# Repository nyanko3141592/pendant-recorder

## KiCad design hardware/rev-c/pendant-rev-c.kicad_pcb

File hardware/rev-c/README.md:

# Rev C0 — 小ささ優先 / USB / 16時間録音を目指す回路

**設計検討版、発注不可。** [V1の範囲](../../docs/v1-scope.md)を優先する。Rev A/Bを上書きしない。回路図、接続表、実フットプリント配置、配線試行、収納モデルを追加した。寸法と電池持ちの成立を保証するものではない。

## 原本

- [回路図PDF](pendant-rev-c.pdf) / [KiCad回路図](pendant-rev-c.kicad_sch) / [SVG](pendant-rev-c.svg)
- [design.json](design.json) / [全端子接続表](connections.csv) / [BOM](bom.csv)
- [KiCad PCB](pendant-rev-c.kicad_pcb) / [部品配置](placement-report.json)
- [検証・発注条件](order-status.json) / [DRC](drc.json) / [ERC](erc.json)
- [ケース構造](../../mechanical/structure-c0/README.md) / [同縮尺比較](../../mechanical/size-comparison-c0/README.md)

## 現時点の検査

ERC 0、回路図とPCBの等価性差分0、260物理パッドのネット所属一致。DRC 5（USB穴クリアランス4、行き止まり配線1）、未接続67。配線は未完了で発注不可。チェックの成功は電気動作・16h動作の検証ではない。

## 回路の変更

76参照（実装部品69点＋基板接点7点）。無線モジュールをSTM32U535CEU6（UFQFPN48、7×7mm、512KB Flash/274KB SRAM、内部LDO版）へ変更。無線回路・アンテナ・RF空間はない。SDはSPIを維持し、48ピン品にSDMMCがない問題を回避する。これはMCU候補を使った回路設計で、量産採用・調達承認ではない。

- USB: PA11/PA12、SWD: PA13/PA14。
- マイク: PB3/PB4をADF1 CCK0/SDI0（AF3）へ。SPIと重複させない。
- SD: PA5/PA6/PA7をSPI1（AF5）、PA4をGPIO CS。
- 48ピンMCUには独立VDDUSB端子がないため、電源を**3.3V**へ変更。3.0V LDOの下限公差をUSB仕様へ当てない。電池終止・LDOドロップアウトによる使用容量減少は実測が必要。
- MAX17048とI2C周辺を外し、1MΩ＋1MΩ分圧と10nFでPA1へ電池電圧を入力。最大4.2Vから2.1V、定常分圧負荷2.1µA。概算残量のみ。VREFINT校正・ADC取得時間・入力漏れとRC整定を検証する。
- USB保護を同シリーズのUSBLC6-2P6/SOT-666へ小型化。ST機能端子表を参照。実装向き・ランド・受理は最終監査待ち。
- T5838＋1.8V LDO＋TXS0104EPWR、4GB SPI SD NAND、BQ25101約21.8mA、NTC＋充電停止、USB負荷分離、保護付き110mAh電池を維持。
- 録音LED＋状態LED、1ボタン。画面・キャラ・無線は追加しない。
- LSE＋内部クロック/USB CRSで動作を検討。水晶・負荷容量・USBクロック精度は未検証。

## サイズ・電力

21×31×0.8mmの4層両面基板へ実フットプリントを配置。上面にUSBとPH端子、裏面に低背部品を置く。電池は基板下へ重ねる。ケース案23.8×34×14mmで、Rev B比で長さ12.5mm減、幅1mm減、厚さ1.2mm増、直方体包絡体積約23%減。22×34×12mmの目標は達成していない。部品が置けたことと配線・組立可能性は別。

110mAh×仮使用率70%=77mAh。16hは電池端平均4.8125mA以下、20hは3.85mA以下という計算条件。3.3V化後の使用率70%は未検証で、実測時間の見積もりとして断定しない。平均2mA/3mA等を実測値として扱わない。

## 発注前の主要残件

- 全結線/DRC、USB差動配線、GND帰路、電源幅、ピン直近デカップリング。自動配置・配線の結果を電気的完成扱いにしない。
- 全ピンと代替機能の独立監査。MCUピン番号はKiCad公式ライブラリから抽出、ST DS14217と最終全数照合待ち。USB共有電源・ADC・起動・低電圧復帰を実機検証。
- 全品番/公差/高さ/在庫/JLC Standard両面実装受理。TBDの水晶、LED等を確定。ソース・BOMに載せただけで購入可能としない。
- PH嵌合プラグ、100mmの未加工線、セル膨張、NTC熱接触、底面マイク音道、ふた固定、紐/クリップ、USBプラグ挿抜クリアランス。
- 16h録音・36h保存・充電中録音・暗号・電源断・3 OS同期。これらのファームは未実装。

## 出典

2026-10-24確認。
- ST: https://www.st.com/en/microcontrollers-microprocessors/stm32u535ce.html
- STM32データシート: https://www.st.com.cn/resource/en/datasheet/stm32u535cb.pdf （DS14217 Rev5、パッケージ/端子/AF表）
- ESD保護: https://www.st.com/resource/en/datasheet/usblc6-2.pdf / https://www.st.com/en/protections-and-emi-filters/usblc6-2.html
- USBLC6-2P6カタログ: https://www.lcsc.com/product-detail/C15999.html （掲載は実装受理・在庫確保ではない）
- 電池・他部品の出典はRev B、docs/battery-sourcing.mdを継承。

## 再生成

`python3 hardware/tools/create_rev_c.py` → `generate_schematic.py rev-c` → `verify_design.py <kicad-cli> rev-c`。KiCad同梱Pythonで `layout_rev_c.py` を実行すると配置から再生成し既存配線を消すため注意。`route_rev_c.py export/import` はローカルFreerouting試行用。最新版の発注可否はorder-status.jsonを読む。

最終メタデータ同期は `sync_rev_c_metadata.py`、検査と発注不可レポート更新はKiCad Pythonで `check_rev_c.py`（未達時exit 2）。

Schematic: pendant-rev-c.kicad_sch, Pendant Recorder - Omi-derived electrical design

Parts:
C1, C2, C3, C6, C9, C22, C23, C24, C26: 100n; C_0402_1005Metric
C4: 10u; C_0603_1608Metric
C5, C15: 4.7u; C_0603_1608Metric
C7, C16, C18, C19, C25: 1u; C_0402_1005Metric
C11, C12: 10p tentative; C_0402_1005Metric
C13: 2.2u 10V; C_0402_1005Metric
C14: 2.2u; C_0402_1005Metric
C27: 22u effective TBD; C_0603_1608Metric
C28: 10n; C_0402_1005Metric
D1: red LED; LED_0402_1005Metric
D2: BAT54WS (candidate; leakage/forward drop review p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; D_SOD-323
D6: amber LED 0402 TBD; LED_0402_1005Metric
J1: USB4105-GF-A (candidate); USB_C_Receptacle_GCT_USB4105-xx-A_16P_TopMnt_Horizontal
J2: S2B-PH-SM4-TB(LF)(SN) / DTP401525 110mAh; JST_PH_S2B-PH-SM4-TB_1x02-1MP_P2.00mm_Horizontal
J3: TC2030 SWD target pads; Tag-Connect_TC2030-IDC-NL_2x03_P1.27mm_Vertical
Q1: DMP2035U (candidate; power path review pending); SOT-23
Q2: 2N7002 (charge inhibit); SOT-23
Q3: 2N7002 (VBUS detect); SOT-23
R1: 0R; R_0402_1005Metric
R2: 10k; R_0402_1005Metric
R3, R4, R11, R12, R13, R15, R16, R17, R22: 100k; R_0402_1005Metric
R5: 3.3k; R_0402_1005Metric
R6, R7: 5.1k 1%; R_0402_1005Metric
R8, R9: 0R tuning; R_0402_1005Metric
R10: 6.19k 1%; R_0402_1005Metric
R14: 1M; R_0402_1005Metric
R21, R23: 22R tentative; R_0402_1005Metric
R24, R25, R28: 47k; R_0402_1005Metric
R32: 6.8k tentative; R_0402_1005Metric
R33, R34: 1M 1%; R_0402_1005Metric
SW1: B3U-1000P (candidate); SW_SPST_B3U-1000P
TH1: NCP15XH103F03RC 10k NTC; R_0402_1005Metric
TP1, TP2, TP3, TP4, TP5, TP6: TestPoint; TestPoint_Pad_D1.0mm
U1: STM32U535CEU6; QFN-48-1EP_7x7mm_P0.5mm_EP5.6x5.6mm
U2: USBLC6-2P6; SOT-666
U3: BQ25101YFPR; BQ25101_YFP6
U4: TPS7A0233PDBVR; SOT-23-5
U6: TPS7A0218PDBVR; SOT-23-5
U8: T5838; T5838_LGA7_BottomPort
U9: TXS0104EPWR; TSSOP-14_4.4x5mm_P0.65mm
U10: TPS22916CYFPR; TPS22916_YFP4
U11: CSNP32GCR01-BOW; CSNP32GCR01_LGA8
Y1: 32.768kHz CL=7pF TBD; Crystal_SMD_2012-2Pin_2.0x1.2mm

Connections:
/BAT: C14.1, J2.1 (PACK+), Q1.3 (D), R33.1, TP1.1, U3.A1 (OUT)
/BAT_ADC: C28.1, R33.2, R34.1, U1.11 (PA1)
/BAT_TS: Q2.3 (D), TH1.1, U3.B1 (TS)
/BOOT0: R3.1, U1.44 (PH3)
/BUTTON_N: R4.2, SW1.1, U1.26 (PB13)
/CC1: J1.A5 (CC1), R6.1
/CC2: J1.B5 (CC2), R7.1
/CHG_DISABLE: Q2.1 (G), R12.1, U1.20 (PB2)
/CHG_N: R11.2, U1.27 (PB14), U3.C1 (CHG)
/GND: C1.2, C2.2, C3.2, C4.2, C5.2, C6.2, C7.2, C9.2, C11.2, C12.2, C13.2, C14.2, C15.2, C16.2, C18.2, C19.2, C22.2, C23.2, C24.2, C25.2, C26.2, C27.2, C28.2, D1.1 (K), D6.1 (K), J1.A1 (GND), J1.A12 (GND), J1.B1 (GND), J1.B12 (GND), J1.SH (SHIELD), J2.2 (PACK-), J3.5 (GND), Q2.2 (S), Q3.2 (S), R3.2, R6.2, R7.2, R10.2, R12.2, R14.2, R16.2, R17.2, R22.2, R34.2, SW1.2, TH1.2, TP6.1, U1.8 (VSSA), U1.23 (VSS), U1.35 (VSS), U1.47 (VSS), U1.49 (VSS), U2.2 (GND), U3.C2 (VSS), U4.2 (GND), U6.2 (GND), U8.2 (SELECT), U8.3 (GND), U9.7 (GND), U10.B1 (GND), U11.4 (VSS)
/ISET: R10.1, U3.B2 (ISET)
/LED_A: D1.2 (A), R5.2
/LSE_IN: C11.1, U1.3 (PC14), Y1.1
/LSE_OUT: C12.1, U1.4 (PC15), Y1.2
/MIC_CLK_1V8: U8.6 (CLK), U9.5 (A4)
/MIC_DATA_1V8: U8.1 (DATA), U9.4 (A3)
/MIC_EN: R17.1, U1.19 (PB1), U6.3 (EN)
/MIC_THSEL: U1.13 (PA3), U9.12 (B2)
/MIC_THSEL_1V8: U8.5 (THSEL), U9.3 (A2)
/MIC_WAKE: U1.12 (PA2), U9.13 (B1)
/MIC_WAKE_1V8: U8.4 (WAKE), U9.2 (A1)
/NRST: C9.1, J3.3 (nRESET), R2.2, U1.7 (NRST)
/PDM_CLK: R21.2, U9.10 (B4)
/PDM_CLK_MCU: R21.1, U1.39 (PB3)
/PDM_DATA: U1.40 (PB4), U9.11 (B3)
/REC_LED: R5.1, U1.25 (PB12)
/SD_CLK: R23.2, U11.3 (CLK)
/SD_CLK_MCU: R23.1, U1.15 (PA5)
/SD_CS_N: R28.2, U1.14 (PA4), U11.2 (CS_N)
/SD_EN: R22.1, U1.18 (PB0), U10.B2 (ON)
/SD_MISO: R25.2, U1.16 (PA6), U11.6 (DO)
/SD_MOSI: R24.2, U1.17 (PA7), U11.5 (DI)
/SD_V3: C26.1, C27.1, R24.1, R25.1, R28.1, TP5.1, U10.A1 (VOUT), U11.8 (VCC)
/STATUS_LED: R32.1, U1.29 (PA8)
/STATUS_LED_A: D6.2 (A), R32.2
/SWCLK: J3.4 (SWCLK), U1.37 (PA14)
/SWDIO: J3.2 (SWDIO), U1.34 (PA13)
/SYS: C15.1, D2.1 (K), Q1.2 (S), TP2.1, U4.1 (IN), U4.3 (EN)
/USB_DM: J1.A7 (D-), J1.B7 (D-), R9.1, U2.3 (IO2), U2.4 (IO2)
/USB_DM_MCU: R9.2, U1.32 (PA11)
/USB_DP: J1.A6 (D+), J1.B6 (D+), R8.1, U2.1 (IO1), U2.6 (IO1)
/USB_DP_MCU: R8.2, U1.33 (PA12)
/V1V8: C18.1, C22.1, C23.1, TP4.1, U6.5 (OUT), U8.7 (VDD), U9.1 (VCCA), U9.8 (OE)
/V3V3: C1.1, C2.1, C3.1, C4.1, C16.1, C19.1, C24.1, C25.1, J3.1 (VTref), R1.1, R2.1, R4.1, R11.1, R15.1, TP3.1, U1.1 (VBAT), U1.24 (VDD), U1.36 (VDD), U1.48 (VDD), U4.5 (OUT), U6.1 (IN), U9.14 (VCCB), U10.A2 (VIN)
/VBUS: C13.1, D2.2 (A), J1.A4 (VBUS), J1.A9 (VBUS), J1.B4 (VBUS), J1.B9 (VBUS), Q1.1 (G), R13.1, R16.1, U2.5 (VBUS), U3.A2 (IN)
/VBUS_GATE: Q3.1 (G), R13.2, R14.1
/VBUS_N: Q3.3 (D), R15.2, U1.10 (PA0)
/VCAP: C5.1, U1.22 (VCAP)
/VDDA: C6.1, C7.1, R1.2, U1.9 (VDDA)

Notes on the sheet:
01 MCU / RTC / UI
02 USB-C / CHARGER
03 POWER / FUEL GAUGE
04 AUDIO / SD / INDICATORS
ENGINEERING DRAFT - NOT FOR FABRICATION - See hardware/rev-c/README.md

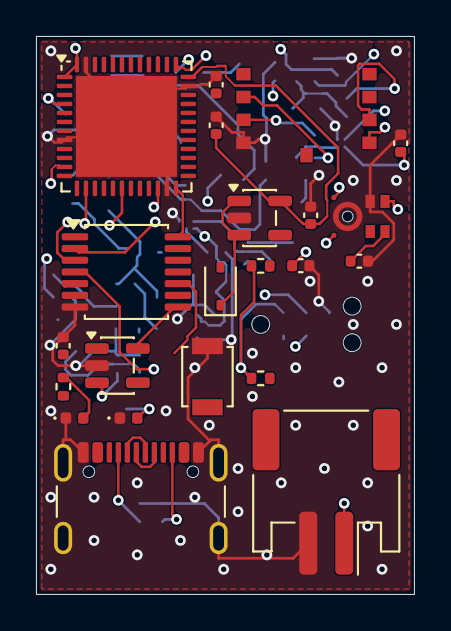
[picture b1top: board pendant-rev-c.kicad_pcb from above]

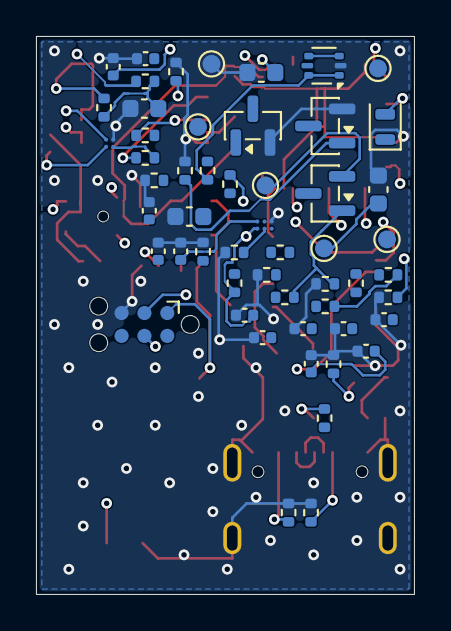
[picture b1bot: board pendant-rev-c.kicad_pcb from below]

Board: 4 copper layers, 21.0 x 31.0 mm, 76 parts (54 on the bottom side), 49 nets.

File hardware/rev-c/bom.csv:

Reference,Part/value,Footprint,Design note
U1,STM32U535CEU6,Package_DFN_QFN:QFN-48-1EP_7x7mm_P0.5mm_EP5.6x5.6mm,512KB Flash/274KB RAM; non-SMPS UFQFPN48. PB3/PB4 ADF AF3; PA5/6/7 SPI1 AF5. VDD USB shared 3.3V. JLC acceptance and pin review pending.
C1,100n,Capacitor_SMD:C_0402_1005Metric,
C4,10u,Capacitor_SMD:C_0603_1608Metric,Main bulk capacitor; check startup and effective capacitance.
C9,100n,Capacitor_SMD:C_0402_1005Metric,
R2,10k,Resistor_SMD:R_0402_1005Metric,
Y1,32.768kHz CL=7pF TBD,Crystal:Crystal_SMD_2012-2Pin_2.0x1.2mm,
C11,10p tentative,Capacitor_SMD:C_0402_1005Metric,
C12,10p tentative,Capacitor_SMD:C_0402_1005Metric,
J3,TC2030 SWD target pads,Connector:Tag-Connect_TC2030-IDC-NL_2x03_P1.27mm_Vertical,TC2030-NL/CTX standard; completed STM32-compatible probe/cable; access with battery disconnected.
SW1,B3U-1000P (candidate),Button_Switch_SMD:SW_SPST_B3U-1000P,
R4,100k,Resistor_SMD:R_0402_1005Metric,
R5,3.3k,Resistor_SMD:R_0402_1005Metric,
D1,red LED,LED_SMD:LED_0402_1005Metric,
J1,USB4105-GF-A (candidate),Connector_USB:USB_C_Receptacle_GCT_USB4105-xx-A_16P_TopMnt_Horizontal,Exact footprint and shield pad numbering pending connector selection
R6,5.1k 1%,Resistor_SMD:R_0402_1005Metric,
R7,5.1k 1%,Resistor_SMD:R_0402_1005Metric,
R8,0R tuning,Resistor_SMD:R_0402_1005Metric,STM32 integrated USB termination; external series value validate against ST USB layout guidance.
R9,0R tuning,Resistor_SMD:R_0402_1005Metric,STM32 integrated USB termination; external series value validate against ST USB layout guidance.
U2,USBLC6-2P6,Package_TO_SOT_SMD:SOT-666,"ST DS4260 same 6-pin function diagram; smaller package, LCSC C15999 catalog; orientation/land pattern final audit pending."
C13,2.2u 10V,Capacitor_SMD:C_0402_1005Metric,
U3,BQ25101YFPR,Pendant:BQ25101_YFP6,"BQ25101, 21.81mA nominal with 6.19k 1%; TS NTC must contact cell. Temperature/timeout validation pending."
R10,6.19k 1%,Resistor_SMD:R_0402_1005Metric,BQ25101: nominal 21.81mA; KISET max145 / (6190*0.99)=23.66mA < DTP max55mA. Standard pack charging approximately22mA.
R11,100k,Resistor_SMD:R_0402_1005Metric,
C14,2.2u,Capacitor_SMD:C_0402_1005Metric,
J2,S2B-PH-SM4-TB(LF)(SN) / DTP401525 110mAh,Connector_JST:JST_PH_S2B-PH-SM4-TB_1x02-1MP_P2.00mm_Horizontal,"Two-pin PH pack connection. Confirm delivered polarity. TH1 is PCB-mounted thermal contact, no third battery wire."
TH1,NCP15XH103F03RC 10k NTC,Resistor_SMD:R_0402_1005Metric,PCB-mounted NTC thermally coupled to pack through insulation. Position/contact/thermal response require validation; no hand-soldered harness.
Q2,2N7002 (charge inhibit),Package_TO_SOT_SMD:SOT-23,High disables charging by pulling TS low; USB suspend policy required
R12,100k,Resistor_SMD:R_0402_1005Metric,
D2,BAT54WS (candidate; leakage/forward drop review pending),Diode_SMD:D_SOD-323,USB path; characterize leakage and input inrush
Q1,DMP2035U (candidate; power path review pending),Package_TO_SOT_SMD:SOT-23,"S=SYS, D=BAT intentionally; body diode BAT -> SYS; exact MPN/pinout pending"
R16,100k,Resistor_SMD:R_0402_1005Metric,
C15,4.7u,Capacitor_SMD:C_0603_1608Metric,
U4,TPS7A0233PDBVR,Package_TO_SOT_SMD:SOT-23-5,3.3V main rail: 48-pin MCU has no separate USB supply; dropout/capacity measurement required.
U6,TPS7A0218PDBVR,Package_TO_SOT_SMD:SOT-23-5,DBV / SOT23-5 prototype; miniaturization later
C16,1u,Capacitor_SMD:C_0402_1005Metric,
C18,1u,Capacitor_SMD:C_0402_1005Metric,
C19,1u,Capacitor_SMD:C_0402_1005Metric,
R17,100k,Resistor_SMD:R_0402_1005Metric,
U8,T5838,Pendant:T5838_LGA7_BottomPort,BOTTOM port; 1.62..1.98V only; SELECT low = right channel
U9,TXS0104EPWR,Package_SO:TSSOP-14_4.4x5mm_P0.65mm,TI SCES651K table 5-3; JLC C44955 exact TSSOP-14 catalog match. Avoid 0.4mm DSBGA central-pad escape requirement.
R21,22R tentative,Resistor_SMD:R_0402_1005Metric,
C22,100n,Capacitor_SMD:C_0402_1005Metric,
C23,100n,Capacitor_SMD:C_0402_1005Metric,
C24,100n,Capacitor_SMD:C_0402_1005Metric,
U10,TPS22916CYFPR,Pendant:TPS22916_YFP4,Omi SD switch; power-off sequence must tristate ALL SD signals
R22,100k,Resistor_SMD:R_0402_1005Metric,
C25,1u,Capacitor_SMD:C_0402_1005Metric,
U11,CSNP32GCR01-BOW,Pendant:CSNP32GCR01_LGA8,SPI mode per manufacturer p2; unused DAT1/DAT2 reserved; verify power-up and interrupted-write behavior.
R23,22R tentative,Resistor_SMD:R_0402_1005Metric,
R24,47k,Resistor_SMD:R_0402_1005Metric,
R25,47k,Resistor_SMD:R_0402_1005Metric,
R28,47k,Resistor_SMD:R_0402_1005Metric,
C26,100n,Capacitor_SMD:C_0402_1005Metric,
C27,22u effective TBD,Capacitor_SMD:C_0603_1608Metric,
TP1,TestPoint,TestPoint:TestPoint_Pad_D1.0mm,
TP2,TestPoint,TestPoint:TestPoint_Pad_D1.0mm,
TP3,TestPoint,TestPoint:TestPoint_Pad_D1.0mm,
TP4,TestPoint,TestPoint:TestPoint_Pad_D1.0mm,
TP5,TestPoint,TestPoint:TestPoint_Pad_D1.0mm,
TP6,TestPoint,TestPoint:TestPoint_Pad_D1.0mm,
R32,6.8k tentative,Resistor_SMD:R_0402_1005Metric,"LED current target 0.1-0.2mA; verify LED Vf, daylight readability and GPIO limits"
D6,amber LED 0402 TBD,LED_SMD:LED_0402_1005Metric,Battery level by blink count; shared charging/error indication; exact LED MPN pending.
C2,100n,Capacitor_SMD:C_0402_1005Metric,
C3,100n,Capacitor_SMD:C_0402_1005Metric,
C5,4.7u,Capacitor_SMD:C_0603_1608Metric,
C6,100n,Capacitor_SMD:C_0402_1005Metric,
C7,1u,Capacitor_SMD:C_0402_1005Metric,
R1,0R,Resistor_SMD:R_0402_1005Metric,
R3,100k,Resistor_SMD:R_0402_1005Metric,
Q3,2N7002 (VBUS detect),Package_TO_SOT_SMD:SOT-23,
R13,100k,Resistor_SMD:R_0402_1005Metric,
R14,1M,Resistor_SMD:R_0402_1005Metric,
R15,100k,Resistor_SMD:R_0402_1005Metric,
R33,1M 1%,Resistor_SMD:R_0402_1005Metric,"Battery divider 1:2; sample after settling, calibrate with VREFINT; not coulomb counting."
R34,1M 1%,Resistor_SMD:R_0402_1005Metric,"Battery divider 1:2; sample after settling, calibrate with VREFINT; not coulomb counting."
C28,10n,Capacitor_SMD:C_0402_1005Metric,"Battery divider 1:2; sample after settling, calibrate with VREFINT; not coulomb counting."

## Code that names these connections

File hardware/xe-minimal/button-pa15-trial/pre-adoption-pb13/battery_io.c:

#include "stm32u5xx_hal.h"
#include "battery_io.h"
void board_battery_io_init(void){
 __HAL_RCC_GPIOA_CLK_ENABLE();
 __HAL_RCC_GPIOB_CLK_ENABLE();
 /* ES0587: use VDD for analog switches, booster disabled.
  * Board VDD is3.3V; low-VDD sampling requirements still apply if rails change. */
 __HAL_RCC_SYSCFG_CLK_ENABLE();
 HAL_SYSCFG_DisableIOAnalogBooster();
 HAL_SYSCFG_EnableIOAnalogVoltageSelection();
 /* PA8 sources R32/D6. Latch off before enabling the output. */
 HAL_GPIO_WritePin(GPIOA,GPIO_PIN_8,GPIO_PIN_RESET);
 GPIO_InitTypeDef pin={0};
 pin.Pin=GPIO_PIN_8;pin.Mode=GPIO_MODE_OUTPUT_PP;
 pin.Pull=GPIO_NOPULL;pin.Speed=GPIO_SPEED_FREQ_LOW;
 HAL_GPIO_Init(GPIOA,&pin);
 /* PA1 is a high-impedance 1M/1M divider with10nF. No digital pulls. */
 /* PB13 BUTTON_N has external100k pull-up R4. */
 pin.Pin=GPIO_PIN_13;pin.Mode=GPIO_MODE_INPUT;pin.Pull=GPIO_NOPULL;
 HAL_GPIO_Init(GPIOB,&pin);
 pin.Pin=GPIO_PIN_1;pin.Mode=GPIO_MODE_ANALOG;pin.Pull=GPIO_NOPULL;
 HAL_GPIO_Init(GPIOA,&pin);
}

bool board_battery_reference_calibration(uint16_t *cal14){
 if(!cal14)return false;
 /* Odd factory address: use byte reads, not an unaligned uint16_t load. */
 volatile const uint8_t *cal=(volatile const uint8_t *)0x0BFA07A5UL;
 uint16_t value=(uint16_t)cal[0]|((uint16_t)cal[1]<<8);
 if(!value||value>=16383)return false;
 *cal14=value;return true;
}

bool board_battery_button_pressed(void){return HAL_GPIO_ReadPin(GPIOB,GPIO_PIN_13)==GPIO_PIN_RESET;}
void board_battery_led(bool on){HAL_GPIO_WritePin(GPIOA,GPIO_PIN_8,on?GPIO_PIN_SET:GPIO_PIN_RESET);}

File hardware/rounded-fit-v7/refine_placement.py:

from pathlib import Path
import json,math,wx
app=wx.App(False)
import pcbnew as k
P=Path(__file__).parent;b=k.LoadBoard(str(P/'outline-only-backup.kicad_pcb'));fs={f.GetReference():f for f in b.GetFootprints()};design={p['ref']:p for p in json.load(open(P/'design.json'))['parts']}
for t in list(b.GetTracks()):b.Delete(t)
def bb(f):
 q=f.GetBoundingBox(False,False);return [k.ToMM(q.GetX()),k.ToMM(q.GetY()),k.ToMM(q.GetWidth()),k.ToMM(q.GetHeight())]
def center(f,x,y):
 a,c,w,h=bb(f);f.Move(k.VECTOR2I(k.FromMM(x-a-w/2),k.FromMM(y-c-h/2)))
center(fs['U2'],19.5,23.5)
center(fs['U10'],21.0,3.1)
movable=[f for r,f in fs.items() if r.startswith(('C','R'))]
occ={'F':[],'B':[[4,2,16,18]]}
for r,f in fs.items():
 if f in movable:continue
 q=bb(f);side='B' if f.IsFlipped() else 'F';occ[side].append(q)
 if any(p.GetDrillSize().x>0 for p in f.Pads()):occ['F' if side=='B' else 'B'].append(q)
targets={'C1':('U1','24'),'C2':('U1','36'),'C3':('U1','48'),'C5':('U1','22'),'C6':('U1','9'),'C7':('U1','9'),'C9':('U1','7'),'C11':('Y1','1'),'C12':('Y1','2'),'C16':('U4','5'),'C15':('U4','1'),'C18':('U6','5'),'C19':('U6','1'),'C22':('U8','7'),'C23':('U9','1'),'C24':('U9','11'),'C25':('U10','A2'),'C26':('U11','8'),'C27':('U11','8'),'C29':('U12','8'),'C13':('J1','A4'),'C14':('U3','A1'),'C4':('U1','24'),'C28':('U1','11'),'R8':('U1','33'),'R9':('U1','32'),'R21':('U1','39'),'R23':('U1','15'),'R6':('J1','A5'),'R7':('J1','B5')}
priority=['C16','C22','C23','C24','C25','C26','C27','C18','C19','C15','C29','C5','C1','C2','C3','C6','C7','C11','C12','R8','R9','R21','R23','C13','C14','C9','C4','C28']
def inside(x,y):
 # 0.25mm inside rounded outline, with cut top y=0.
 if y<.25:return False
 qx=abs(x-12)-8;qy=abs(y-12.5)-10.5
 return math.hypot(max(qx,0),max(qy,0))+min(max(qx,qy),0)<=3.75
for f in sorted(movable,key=lambda f:priority.index(f.GetReference()) if f.GetReference() in priority else 100):
 ref=f.GetReference();target=targets.get(ref)
 if target:
  parent=fs[target[0]];pad=next(p for p in parent.Pads() if p.GetNumber()==target[1]);tx,ty=k.ToMM(pad.GetPosition().x),k.ToMM(pad.GetPosition().y);preferred='B' if parent.IsFlipped() else 'F'
 else:
  nets={p['net'] for p in design[ref]['pins'] if p['net'] not in ['GND','V3V3','VBUS','BAT','SYS',None]};pads=[p for r,ff in fs.items() if ff not in movable for p in ff.Pads() if p.GetNetname().lstrip('/') in nets]
  tx=sum(k.ToMM(p.GetPosition().x) for p in pads)/len(pads) if pads else 12;ty=sum(k.ToMM(p.GetPosition().y) for p in pads)/len(pads) if pads else 13;preferred='F'
 best=None
 for side in ['F','B']:
  if f.IsFlipped()!=(side=='B'):f.Flip(f.GetPosition(),False)
  for rot in [0,90,180,270]:
   f.SetOrientationDegrees(rot);a,c,w,h=bb(f)
   for iy in range(1,107):
    y=iy*.25
    for ix in range(1,95):
     x=ix*.25
     if not all(inside(xx,yy) for xx in [x,x+w] for yy in [y,y+h]):continue
     if any(not(x+w+.15<=a or a+c+.15<=x or y+h+.15<=d or d+e+.15<=y) for a,d,c,e in occ[side]):continue
     score=(x+w/2-tx)**2+(y+h/2-ty)**2+(2 if side!=preferred else 0)
     if best is None or score<best[0]:best=(score,x+w/2,y+h/2,side,rot)
 if best is None:raise RuntimeError('no space '+ref)
 _,x,y,side,rot=best
 if f.IsFlipped()!=(side=='B'):f.Flip(f.GetPosition(),False)
 f.SetOrientationDegrees(rot);center(f,x,y);occ[side].append(bb(f));print(ref,round(math.sqrt(best[0]),2),side,flush=True)
k.SaveBoard(str(P/'pendant-compact-100-v5.kicad_pcb'),b);assert k.ExportSpecctraDSN(b,str(P/'route.dsn'))
out=[]
for f in fs.values():
 x,y,w,h=bb(f);out.append(dict(ref=f.GetReference(),x=x+w/2,y=y+h/2,w=w,h=h,side='B' if f.IsFlipped() else 'F',rotation=f.GetOrientationDegrees()))
(P/'placement.json').write_text(json.dumps(out,indent=2))
